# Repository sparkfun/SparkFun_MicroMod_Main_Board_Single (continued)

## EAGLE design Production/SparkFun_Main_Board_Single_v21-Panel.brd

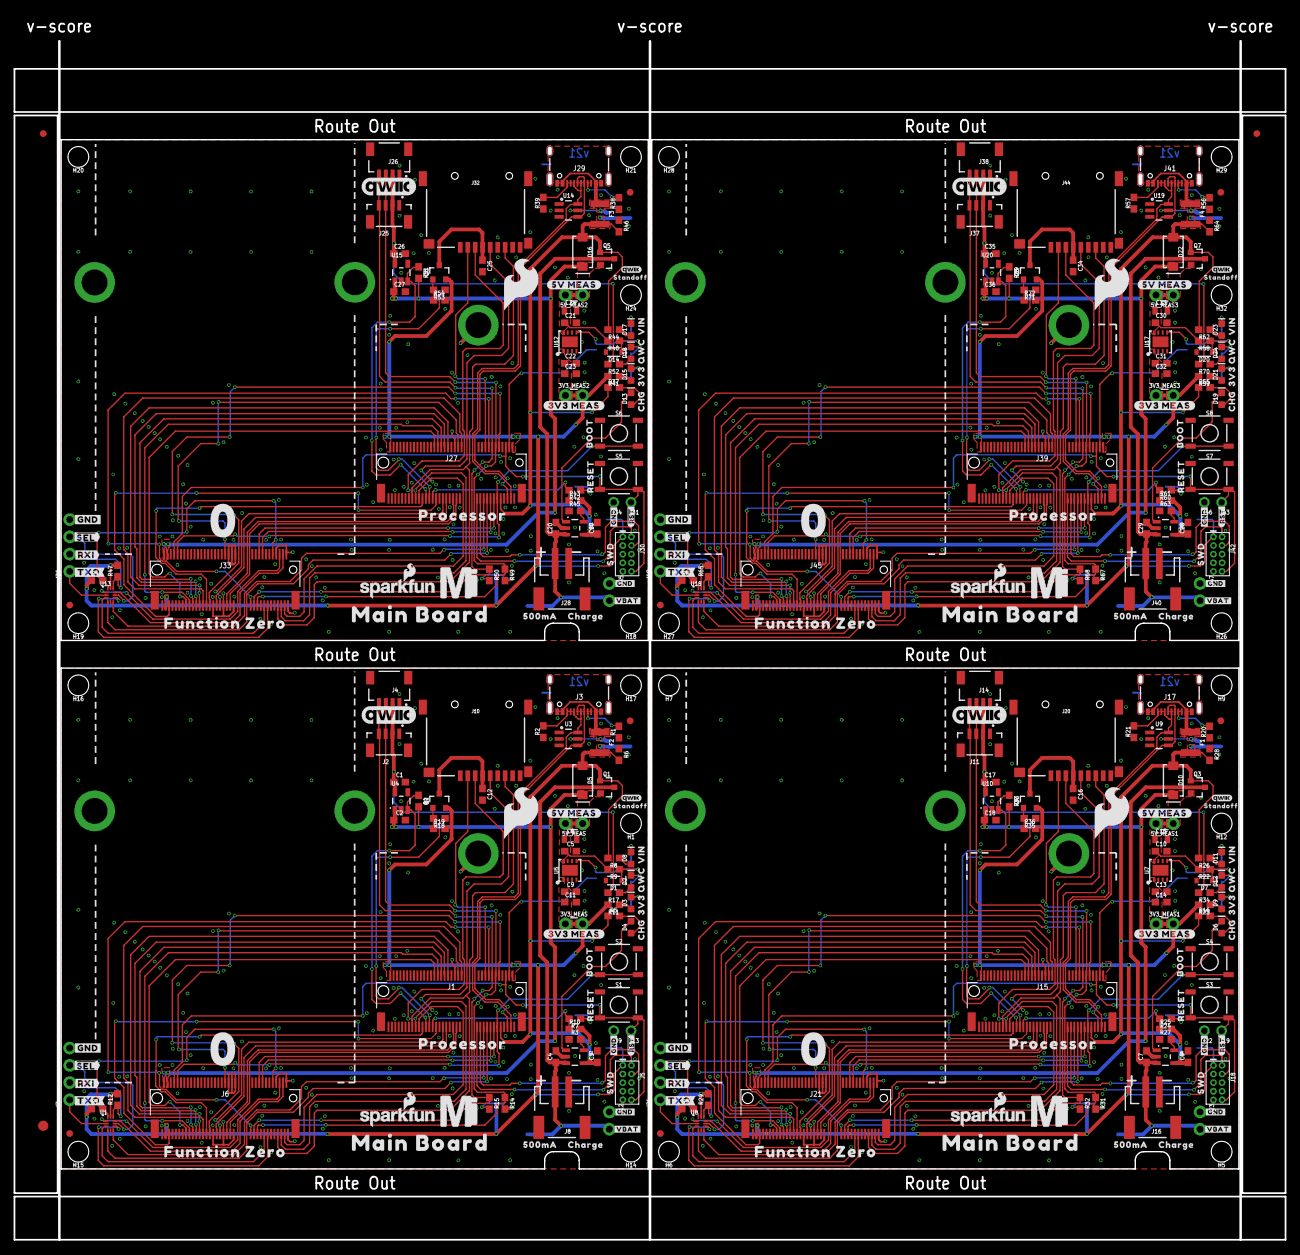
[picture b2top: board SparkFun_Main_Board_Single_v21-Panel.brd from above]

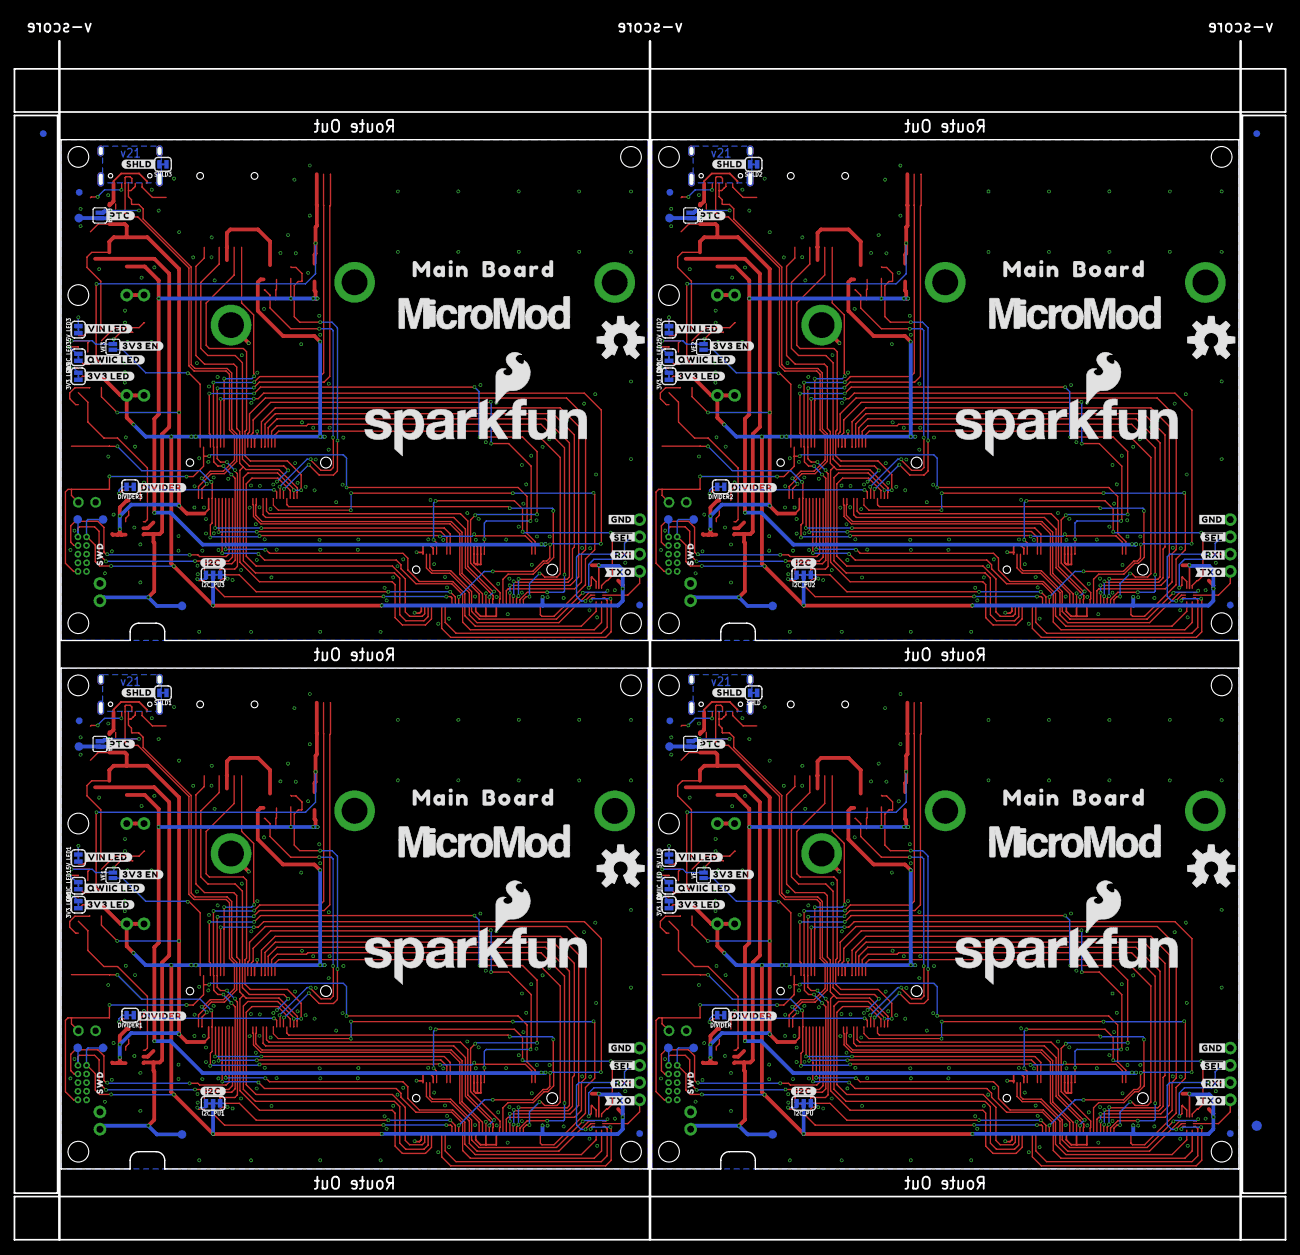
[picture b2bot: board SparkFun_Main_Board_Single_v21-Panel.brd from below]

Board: 2 copper layers, 186.9 x 176.3 mm, 518 parts (131 on the bottom side), 280 nets.

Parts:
3V3_LED, 3V3_LED1, 3V3_LED2, 3V3_LED3, 5V_LED, 5V_LED1, 5V_LED2, 5V_LED3: JUMPER-SMT_2_NC_TRACE_SILK; SMT-JUMPER_2_NC_TRACE_SILK
3V3_MEAS, 3V3_MEAS1, 3V3_MEAS2, 3V3_MEAS3, 5V_MEAS, 5V_MEAS1, 5V_MEAS2, 5V_MEAS3: JUMPER-COMBO_2_NC_TRACE; COMBO-JUMPER_2_NC_TRACE
BYP, BYP1, BYP2, BYP3: JUMPER-SMT_2_NO_SILK; SMT-JUMPER_2_NO_SILK
C1, C2, C17, C18, C26, C27, C35, C36: 1.0uF; 0603
C3, C4, C6, C7, C11, C14, C19, C20, C23, C28, C29, C32: 4.7uF; 0603
C5, C10, C21, C30: 0.1uF; 0603
C8, C15, C24, C33: 10uF; 0805
C9, C12, C13, C16, C22, C25, C31, C34: 10uF; 0603
D1, D7, D14, D20: 3.3V; SOD-323
D2, D3, D8, D9, D11, D12, D15, D17, D18, D21, D23, D24: RED; LED-0603
D4, D6, D13, D19: Yellow; LED-0603
D5, D10, D16, D22: 3A/40V/500mV; SMA-DIODE
DIVIDER, DIVIDER1, DIVIDER2, DIVIDER3: JUMPER-SMT_2_NC_TRACE_SILK; SMT-JUMPER_2_NC_TRACE_SILK
E$1, E$2, E$3, E$4: FIDUCIAL-1X2
E$5, E$6: FIDUCIAL-1.5X3
F1, F2, F3, F4: 6V/2A; 1210
FD1, FD2, FD3, FD4, FD5, FD6, FD7, FD8, FD9, FD10, FD11, FD12, FD13, FD14, FD15, FD16: FIDUCIAL1X2; FIDUCIAL-1X2
H1, H5, H6, H7, H9, H12, H14, H15, H16, H17, H18, H19, H20, H21, H24, H26, H27, H28, H29, H32: STAND-OFFTIGHT; STAND-OFF-TIGHT
H2, H3, H4, H8, H10, H11, H13, H22, H23, H25, H30, H31: STAND-OFF-REFLOW-M2.5_2.5MM_TALL; STAND-OFF-REFLOW-M2.5
I2C_PU, I2C_PU1, I2C_PU2, I2C_PU3: JUMPER-SMT_3_2-NC_TRACE_SILK; SMT-JUMPER_3_2-NC_TRACE_SILK
J1, J15, J27, J39: MICROMOD-2222-C; M.2-CONNECTOR-E
J2, J11, J25, J37: Vertical Qwiic Connector; JST04_1MM_VERT
J3, J17, J29, J41: USB-C-16P-2LAYER-PADS
J4, J14, J26, J38: QWIIC_RIGHT_ANGLE; JST04_1MM_RA
J5, J18, J30, J42: CORTEX_JTAG_DEBUG_MINIMUM_PTH; 2X5-PTH-1.27MM
J6, J21, J33, J45: MICROMOD_FUNCTION_MAIN; M.2-CONNECTOR-E-FUNCTION-STANDARD
J7, J24, J36, J48: 1X04_NO_SILK
J8, J16, J28, J40: JST-2-SMD
J9, J13, J19, J22, J31, J34, J43, J46: 1X01_NO_SILK
J10, J20, J32, J44: MICRO-SD-PUSH-PUSH-EXT-PIN; MICROSD-EXTERNALPIN
J12, J23, J35, J47: 1X02_NO_SILK
LOGO1, LOGO4, LOGO7, LOGO10: QWIIC_LOGO_8MM; QWIIC_8MM
LOGO2, LOGO5, LOGO8, LOGO11: SFE_LOGO_NAME_FLAME.3_INCH; SFE_LOGO_NAME_FLAME_.3
LOGO3, LOGO6, LOGO9, LOGO12: OSHW-LOGOL; OSHW-LOGO-L
Q1, Q3, Q5, Q7: 3.1A/30V/105mΩ; SOT23-3
Q2, Q4, Q6, Q8: 20V/4.2A/52mΩ/1.4W; SOT23-3
QWIIC_LED, QWIIC_LED1, QWIIC_LED2, QWIIC_LED3: JUMPER-SMT_2_NC_TRACE_SILK; SMT-JUMPER_2_NC_TRACE_SILK
R1, R2, R20, R21, R38, R39, R56, R57: 5.1k; 0603
R3, R27, R45, R63: 2.0k; 0603
R4, R9, R12, R13, R19, R22, R29, R30, R33, R36, R40, R47, R48, R51, R54, R58, R65, R66, R69, R72: 100k; 0603
R5, R16, R37, R55: 4.7k; 0603
R6, R7, R24, R28, R42, R46, R60, R64: 10k; 0603
R8, R14, R15, R26, R31, R32, R44, R49, R50, R62, R67, R68: 2.2k; 0603
R10, R25, R43, R61: 20k; 0603
R11, R17, R23, R34, R41, R52, R59, R70: 1k; 0603
R18, R35, R53, R71: 100; 0603
S1, S3, S5, S7: Reset; TACTILE_SWITCH_SMD_5.2MM
S2, S4, S6, S8: BOOT; TACTILE_SWITCH_SMD_5.2MM
SHLD, SHLD1, SHLD2, SHLD3: JUMPER-SMT_2_NC_TRACE_SILK; SMT-JUMPER_2_NC_TRACE_SILK
TP1, TP2, TP3, TP4, TP5, TP6, TP7, TP8, TP9, TP10, TP11, TP12, TP13, TP14, TP15, TP16: TEST-POINT3X5; PAD.03X.05
U1, U8, U13, U18: STG3856QTR; STG3856
U2, U6, U11, U16: MCP73831; SOT23-5
U3, U9, U14, U19: ESD Diode; SOT-23-6
U4, U10, U15, U20: AP7347DQ-33W5-7K-3.3V; SOT25
U5, U7, U12, U17: AP7361C-33; UDFN-8
U$1, U$78, U$122, U$166: #TXO#7
U$2, U$79, U$123, U$167: #RXI#6
U$3, U$84, U$128, U$172: #PTC#15
U$4, U$40, U$89, U$133: 3V332533
U$5, U$41, U$90, U$134: VIN32532
U$6, U$42, U$91, U$135: CHG32531
U$7, U$62, U$106, U$150: #SHLD#501
U$8, U$43, U$92, U$136: BOOT32541
U$9, U$44, U$93, U$137: RESET32540
U$10, U$45, U$94, U$138: PROCESSOR525
U$11, U$46, U$95, U$139: FUNCTION_ZERO520
U$12, U$80, U$124, U$168: ##SEL##5
U$13, U$54, U$98, U$142: MAIN523
U$14, U$47, U$96, U$140: MICROMOD_MI_LOGO_1
U$15, U$48, U$97, U$141: 0523
U$16, U$29, U$73, U$74, U$117, U$118, U$161, U$162: #GND#3
U$17, U$57, U$101, U$145: MICROMOD_LOGO_1
U$18, U$55, U$99, U$143: BOARD524
U$19, U$81, U$125, U$169: ##SEL##3
U$20, U$82, U$126, U$170: #RXI#4
U$21, U$56, U$100, U$144: MAIN_BOARD5523
U$22, U$58, U$102, U$146: QWIIC_3MM
U$23, U$59, U$103, U$147: STANDOFF501
U$24, U$60, U$104, U$148: SFE_LOGO_FLAME_.3
U$25, U$32, U$66, U$75, U$110, U$119, U$154, U$163: SWD6522
U$26, U$63, U$107, U$151: #3V3_MEAS#6522
U$27, U$61, U$105, U$149: CHARGE501
U$28, U$83, U$127, U$171: #TXO#5
U$30, U$72, U$116, U$160: #I2C#501
U$31, U$64, U$108, U$152: #5V_MEAS#6522
U$33, U$65, U$109, U$153: 500MA6520
U$34, U$76, U$120, U$164: SFE_LOGO_NAME_FLAME_.1
U$35, U$77, U$121, U$165: QWC4
U$36, U$37, U$85, U$86, U$129, U$130, U$173, U$174: #GND#10
U$38, U$87, U$131, U$175: ##RST##8
U$39, U$88, U$132, U$176: #VBAT#9
U$49, U$67, U$111, U$155: #3V3_EN#23
U$50, U$68, U$112, U$156: #3V3_LED#22
U$51, U$69, U$113, U$157: #QWIIC_LED#22
U$52, U$70, U$114, U$158: #DIVIDER#23
U$53, U$71, U$115, U$159: #VIN_LED#24
VE, VE1, VE2, VE3: JUMPER-SMT_2_NO_SILK; SMT-JUMPER_2_NO_SILK

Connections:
3.3V: 3V3_MEAS.2, 3V3_MEAS.4, I2C_PU.2, J1.2, J1.74, J5.1, J6.73, Q2.2, R11.2, R12.2, R13.1, TP2.1, U1.P11
3.3V1: 3V3_MEAS1.2, 3V3_MEAS1.4, I2C_PU1.2, J15.2, J15.74, J18.1, J21.73, Q4.2, R23.2, R29.2, R30.1, TP5.1, U8.P11
3.3V2: 3V3_MEAS2.2, 3V3_MEAS2.4, I2C_PU2.2, J27.2, J27.74, J30.1, J33.73, Q6.2, R41.2, R47.2, R48.1, TP9.1, U13.P11
3.3V3: 3V3_MEAS3.2, 3V3_MEAS3.4, I2C_PU3.2, J39.2, J39.74, J42.1, J45.73, Q8.2, R59.2, R65.2, R66.1, TP13.1, U18.P11
3.3V_EN: J1.4, VE.1
3.3V_EN1: J15.4, VE1.1
3.3V_EN2: J27.4, VE2.1
3.3V_EN3: J39.4, VE3.1
3.3V_EN_VE: D1.C, R9.1, U5.5, VE.2
3.3V_EN_VE1: D7.C, R22.1, U7.5, VE1.2
3.3V_EN_VE2: D14.C, R40.1, U12.5, VE2.2
3.3V_EN_VE3: D20.C, R58.1, U17.5, VE3.2
3.3V_QWIIC: C1.1, J2.2, J4.2, R17.2, U4.5
3.3V_QWIIC1: C17.1, J11.2, J14.2, R34.2, U10.5
3.3V_QWIIC2: C26.1, J25.2, J26.2, R52.2, U15.5
3.3V_QWIIC3: C35.1, J37.2, J38.2, R70.2, U20.5
3V3_MEAS: 3V3_MEAS.1, 3V3_MEAS.3, C9.1, C11.1, U5.1
3V3_MEAS1: 3V3_MEAS1.1, 3V3_MEAS1.3, C13.1, C14.1, U7.1
3V3_MEAS2: 3V3_MEAS2.1, 3V3_MEAS2.3, C22.1, C23.1, U12.1
3V3_MEAS3: 3V3_MEAS3.1, 3V3_MEAS3.3, C31.1, C32.1, U17.1
!BOOT!: J1.11, J6.66, S2.3, S2.4
!BOOT!1: J15.11, J21.66, S4.3, S4.4
!BOOT!2: J27.11, J33.66, S6.3, S6.4
!BOOT!3: J39.11, J45.66, S8.3, S8.4
!CS0!-PROCESSOR: J1.55, J6.49
!CS0!-PROCESSOR1: J15.55, J21.49
!CS0!-PROCESSOR2: J27.55, J33.49
!CS0!-PROCESSOR3: J39.55, J45.49
!DFU-FC0!: J6.10, R13.2, U1.P12
!DFU-FC0!1: J21.10, R30.2, U8.P12
!DFU-FC0!2: J33.10, R48.2, U13.P12
!DFU-FC0!3: J45.10, R66.2, U18.P12
!RESET!: J1.6, J5.10, J6.68, J13.1, S1.3, S1.4
!RESET!1: J15.6, J18.10, J19.1, J21.68, S3.3, S3.4
!RESET!2: J27.6, J30.10, J31.1, J33.68, S5.3, S5.4
!RESET!3: J39.6, J42.10, J43.1, J45.68, S7.3, S7.4
!SEL!/2IN: J7.3, R12.1, U1.P10
!SEL!/2IN1: J24.3, R29.1, U8.P10
!SEL!/2IN2: J36.3, R47.1, U13.P10
!SEL!/2IN3: J48.3, R65.1, U18.P10
A0-PROCESSOR: J1.34, J6.38
A0-PROCESSOR1: J15.34, J21.38
A0-PROCESSOR2: J27.34, J33.38
A0-PROCESSOR3: J39.34, J45.38
CTS1-PROCESSOR: J1.15, J6.16
CTS1-PROCESSOR1: J15.15, J21.16
CTS1-PROCESSOR2: J27.15, J33.16
CTS1-PROCESSOR3: J39.15, J45.16
D0-PROCESSOR: J1.10, J6.47
D0-PROCESSOR1: J15.10, J21.47
D0-PROCESSOR2: J27.10, J33.47
D0-PROCESSOR3: J39.10, J45.47
D1-PROCESSOR/SD_CARD_!CS!: J1.18, J10.2
D1-PROCESSOR/SD_CARD_!CS!1: J15.18, J20.2
D1-PROCESSOR/SD_CARD_!CS!2: J27.18, J32.2
D1-PROCESSOR/SD_CARD_!CS!3: J39.18, J44.2
D+: J1.3, J3.A6, J3.B6, U3.6
D+1: J15.3, J17.A6, J17.B6, U9.6
D+2: J27.3, J29.A6, J29.B6, U14.6
D+3: J39.3, J41.A6, J41.B6, U19.6
D-: J1.5, J3.A7, J3.B7, U3.4
D-1: J15.5, J17.A7, J17.B7, U9.4
D-2: J27.5, J29.A7, J29.B7, U14.4
D-3: J39.5, J41.A7, J41.B7, U19.4
G0-PROCESSOR: J1.40, J6.53
G0-PROCESSOR1: J15.40, J21.53
G0-PROCESSOR2: J27.40, J33.53
G0-PROCESSOR3: J39.40, J45.53
G1-PROCESSOR: J1.42, J6.55
G1-PROCESSOR1: J15.42, J21.55
G1-PROCESSOR2: J27.42, J33.55
G1-PROCESSOR3: J39.42, J45.55
G2-PROCESSOR: J1.44, J6.57
G2-PROCESSOR1: J15.44, J21.57
G2-PROCESSOR2: J27.44, J33.57
G2-PROCESSOR3: J39.44, J45.57
G3-PROCESSOR: J1.46, J6.59
G3-PROCESSOR1: J15.46, J21.59
G3-PROCESSOR2: J27.46, J33.59
G3-PROCESSOR3: J39.46, J45.59
G4-PROCESSOR: J1.48, J6.61
G4-PROCESSOR1: J15.48, J21.61
G4-PROCESSOR2: J27.48, J33.61
G4-PROCESSOR3: J39.48, J45.61
GND: 3V3_LED.1, 5V_LED.1, C1.2, C2.2, C3.2, C4.2, C5.2, C8.2, C9.2, C11.2, C12.2, D1.A, DIVIDER.1, H2.1, H4.1, H8.1, J1.1, J1.7, J1.33, J1.36, J1.39, J1.45, J1.75, J2.1, J3.GND, J3.GND2, J4.1, J5.3, J5.5, J5.9, J6.1, J6.2, J6.8, J6.32, J6.33, J6.34, J6.36, J6.39, J6.45, J6.75, J7.4, J8.1, J9.1, J10.6, J10.10, J10.11, J10.12, J10.13, J12.1, QWIIC_LED.1, R1.1, R2.1, R3.1, R6.1, R19.2, S1.1, S1.2, S2.1, S2.2, SHLD.1, U1.P5, U2.2, U3.2, U4.2, U5.4, U5.EP
GND1: 3V3_LED1.1, 5V_LED1.1, C6.2, C7.2, C10.2, C13.2, C14.2, C15.2, C16.2, C17.2, C18.2, D7.A, DIVIDER1.1, H3.1, H10.1, H11.1, J11.1, J14.1, J15.1, J15.7, J15.33, J15.36, J15.39, J15.45, J15.75, J16.1, J17.GND, J17.GND2, J18.3, J18.5, J18.9, J20.6, J20.10, J20.11, J20.12, J20.13, J21.1, J21.2, J21.8, J21.32, J21.33, J21.34, J21.36, J21.39, J21.45, J21.75, J22.1, J23.1, J24.4, QWIIC_LED1.1, R20.1, R21.1, R27.1, R28.1, R36.2, S3.1, S3.2, S4.1, S4.2, SHLD1.1, U6.2, U7.4, U7.EP, U8.P5, U9.2, U10.2
GND2: 3V3_LED2.1, 5V_LED2.1, C19.2, C20.2, C21.2, C22.2, C23.2, C24.2, C25.2, C26.2, C27.2, D14.A, DIVIDER2.1, H13.1, H22.1, H23.1, J25.1, J26.1, J27.1, J27.7, J27.33, J27.36, J27.39, J27.45, J27.75, J28.1, J29.GND, J29.GND2, J30.3, J30.5, J30.9, J32.6, J32.10, J32.11, J32.12, J32.13, J33.1, J33.2, J33.8, J33.32, J33.33, J33.34, J33.36, J33.39, J33.45, J33.75, J34.1, J35.1, J36.4, QWIIC_LED2.1, R38.1, R39.1, R45.1, R46.1, R54.2, S5.1, S5.2, S6.1, S6.2, SHLD2.1, U11.2, U12.4, U12.EP, U13.P5, U14.2, U15.2
GND3: 3V3_LED3.1, 5V_LED3.1, C28.2, C29.2, C30.2, C31.2, C32.2, C33.2, C34.2, C35.2, C36.2, D20.A, DIVIDER3.1, H25.1, H30.1, H31.1, J37.1, J38.1, J39.1, J39.7, J39.33, J39.36, J39.39, J39.45, J39.75, J40.1, J41.GND, J41.GND2, J42.3, J42.5, J42.9, J44.6, J44.10, J44.11, J44.12, J44.13, J45.1, J45.2, J45.8, J45.32, J45.33, J45.34, J45.36, J45.39, J45.45, J45.75, J46.1, J47.1, J48.4, QWIIC_LED3.1, R56.1, R57.1, R63.1, R64.1, R72.2, S7.1, S7.2, S8.1, S8.2, SHLD3.1, U16.2, U17.4, U17.EP, U18.P5, U19.2, U20.2
HOST_D+: J1.35, J6.35
HOST_D+1: J15.35, J21.35
HOST_D+2: J27.35, J33.35
HOST_D+3: J39.35, J45.35
HOST_D-: J1.37, J6.37
HOST_D-1: J15.37, J21.37
HOST_D-2: J27.37, J33.37
HOST_D-3: J39.37, J45.37
I2C_!INT!: J1.16, J6.23
I2C_!INT!1: J15.16, J21.23
I2C_!INT!2: J27.16, J33.23
I2C_!INT!3: J39.16, J45.23
I2C_SCL: J1.14, J2.4, J4.4, J6.21, R15.1
I2C_SCL1: J11.4, J14.4, J15.14, J21.21, R32.1
I2C_SCL1-PROCESSOR/QWIIC_EN: J1.53, R4.1, U4.3
I2C_SCL1-PROCESSOR/QWIIC_EN1: J15.53, R33.1, U10.3
I2C_SCL1-PROCESSOR/QWIIC_EN2: J27.53, R51.1, U15.3
I2C_SCL1-PROCESSOR/QWIIC_EN3: J39.53, R69.1, U20.3
I2C_SCL2: J25.4, J26.4, J27.14, J33.21, R50.1
I2C_SCL3: J37.4, J38.4, J39.14, J45.21, R68.1
I2C_SDA: J1.12, J2.3, J4.3, J6.19, R14.1
I2C_SDA1: J11.3, J14.3, J15.12, J21.19, R31.1
I2C_SDA1-PROCESSOR/!SD_ENABLE!: J1.51, R18.1
I2C_SDA1-PROCESSOR/!SD_ENABLE!1: J15.51, R35.1
I2C_SDA1-PROCESSOR/!SD_ENABLE!2: J27.51, R53.1
I2C_SDA1-PROCESSOR/!SD_ENABLE!3: J39.51, R71.1
I2C_SDA2: J25.3, J26.3, J27.12, J33.19, R49.1
I2C_SDA3: J37.3, J38.3, J39.12, J45.19, R67.1
unnamed: J17.B5, R21.2
unnamed: 5V_LED.2, D8.C
unnamed: D3.A, R11.1
unnamed: J3.B5, R2.2
unnamed: J3.A5, R1.2
unnamed: R3.2, U2.5
unnamed: DIVIDER.2, R7.1
unnamed: D4.C, U2.1
unnamed: D4.A, R5.2
unnamed: 3V3_LED.2, D3.C
unnamed: I2C_PU.3, R14.2
unnamed: D8.A, R8.1
unnamed: I2C_PU.1, R15.2
unnamed: D2.A, R17.1
unnamed: D2.C, QWIIC_LED.2
unnamed: C12.1, J10.4, Q2.3
unnamed: J17.A5, R20.2
unnamed: Q2.1, R18.2, R19.1
unnamed: D9.A, R23.1
unnamed: D11.A, R26.1
unnamed: 5V_LED1.2, D11.C
unnamed: 3V3_LED1.2, D9.C
unnamed: I2C_PU1.3, R31.2
unnamed: I2C_PU1.1, R32.2
unnamed: R27.2, U6.5
unnamed: DIVIDER1.2, R24.1
unnamed: D6.C, U6.1
unnamed: D6.A, R16.2
unnamed: D12.A, R34.1
unnamed: D12.C, QWIIC_LED1.2
unnamed: Q4.1, R35.2, R36.1
unnamed: C16.1, J20.4, Q4.3
unnamed: J29.B5, R39.2
unnamed: J29.A5, R38.2
unnamed: D15.A, R41.1
unnamed: D17.A, R44.1
unnamed: 5V_LED2.2, D17.C
unnamed: 3V3_LED2.2, D15.C
unnamed: I2C_PU2.3, R49.2
unnamed: I2C_PU2.1, R50.2
unnamed: R45.2, U11.5
unnamed: DIVIDER2.2, R42.1
unnamed: D13.C, U11.1
unnamed: D13.A, R37.2
unnamed: D18.A, R52.1
unnamed: D18.C, QWIIC_LED2.2
unnamed: Q6.1, R53.2, R54.1
unnamed: C25.1, J32.4, Q6.3
unnamed: J41.B5, R57.2
unnamed: J41.A5, R56.2
unnamed: D21.A, R59.1
unnamed: D23.A, R62.1
unnamed: 5V_LED3.2, D23.C
unnamed: 3V3_LED3.2, D21.C
unnamed: I2C_PU3.3, R67.2
unnamed: I2C_PU3.1, R68.2
unnamed: R63.2, U16.5
unnamed: DIVIDER3.2, R60.1
unnamed: D19.C, U16.1
unnamed: D19.A, R55.2
unnamed: D24.A, R70.1
unnamed: D24.C, QWIIC_LED3.2
unnamed: Q8.1, R71.2, R72.1
unnamed: C34.1, J44.4, Q8.3
PROCESSOR_CAN-RX: J1.41, J6.43
PROCESSOR_CAN-RX1: J15.41, J21.43
PROCESSOR_CAN-RX2: J27.41, J33.43
PROCESSOR_CAN-RX3: J39.41, J45.43
PROCESSOR_CAN-TX: J1.43, J6.41
PROCESSOR_CAN-TX1: J15.43, J21.41
PROCESSOR_CAN-TX2: J27.43, J33.41
PROCESSOR_CAN-TX3: J39.43, J45.41
PWM0-PROCESSOR: J1.32, J6.51
PWM0-PROCESSOR1: J15.32, J21.51
PWM0-PROCESSOR2: J27.32, J33.51
PWM0-PROCESSOR3: J39.32, J45.51
PWR_EN0: J1.47, J6.71
PWR_EN1: J15.47, J21.71
PWR_EN2: J27.47, J33.71
PWR_EN3: J39.47, J45.71
RTS1-PROCESSOR: J1.13, J6.18
RTS1-PROCESSOR1: J15.13, J21.18
RTS1-PROCESSOR2: J27.13, J33.18
RTS1-PROCESSOR3: J39.13, J45.18
RX1-DFU_TX-FC0-PLEX: J6.4, U1.P9
RX1-DFU_TX-FC0-PLEX1: J21.4, U8.P9
RX1-DFU_TX-FC0-PLEX2: J33.4, U13.P9
RX1-DFU_TX-FC0-PLEX3: J45.4, U18.P9
RX1-PROCESSOR: J1.19, U1.P6
RX1-PROCESSOR1: J15.19, U8.P6
RX1-PROCESSOR2: J27.19, U13.P6
RX1-PROCESSOR3: J39.19, U18.P6
RX1-PROCESSOR-PLEX: J6.13, U1.P7
RX1-PROCESSOR-PLEX1: J21.13, U8.P7
RX1-PROCESSOR-PLEX2: J33.13, U13.P7
RX1-PROCESSOR-PLEX3: J45.13, U18.P7
RX1/2S1: J24.2, U8.P8
RX1/2S2: J7.2, U1.P8
RX1/2S3: J36.2, U13.P8
RX1/2S4: J48.2, U18.P8
SHLD: J3.SHLD1, J3.SHLD2, J3.SHLD3, J3.SHLD4, SHLD.2
SHLD1: J17.SHLD1, J17.SHLD2, J17.SHLD3, J17.SHLD4, SHLD1.2
SHLD2: J29.SHLD1, J29.SHLD2, J29.SHLD3, J29.SHLD4, SHLD2.2
SHLD3: J41.SHLD1, J41.SHLD2, J41.SHLD3, J41.SHLD4, SHLD3.2
SPI_PROCESSOR_SCK: J1.57, J6.3, J10.5
SPI_PROCESSOR_SCK1: J15.57, J20.5, J21.3
SPI_PROCESSOR_SCK2: J27.57, J32.5, J33.3
SPI_PROCESSOR_SCK3: J39.57, J44.5, J45.3
SPI_PROCESSOR_SDI: J1.61, J6.7, J10.7
SPI_PROCESSOR_SDI1: J15.61, J20.7, J21.7
SPI_PROCESSOR_SDI2: J27.61, J32.7, J33.7
SPI_PROCESSOR_SDI3: J39.61, J44.7, J45.7
SPI_PROCESSOR_SDO: J1.59, J6.5, J10.3
SPI_PROCESSOR_SDO1: J15.59, J20.3, J21.5
SPI_PROCESSOR_SDO2: J27.59, J32.3, J33.5
SPI_PROCESSOR_SDO3: J39.59, J44.3, J45.5
SWDCK: J1.21, J5.4
SWDCK1: J15.21, J18.4
SWDCK2: J27.21, J30.4
SWDCK3: J39.21, J42.4
SWDIO: J1.23, J5.2, TP1.1
SWDIO1: J15.23, J18.2, TP8.1
SWDIO2: J27.23, J30.2, TP12.1
SWDIO3: J39.23, J42.2, TP16.1
TX1-DFU_RX-FC0-PLEX: J6.6, U1.P1
TX1-DFU_RX-FC0-PLEX1: J21.6, U8.P1
TX1-DFU_RX-FC0-PLEX2: J33.6, U13.P1
TX1-DFU_RX-FC0-PLEX3: J45.6, U18.P1
TX1-PROCESSOR: J1.17, U1.P4
TX1-PROCESSOR1: J15.17, U8.P4
TX1-PROCESSOR2: J27.17, U13.P4
TX1-PROCESSOR3: J39.17, U18.P4
TX1-PROCESSOR-PLEX: J6.15, U1.P3
TX1-PROCESSOR-PLEX1: J21.15, U8.P3
TX1-PROCESSOR-PLEX2: J33.15, U13.P3
TX1-PROCESSOR-PLEX3: J45.15, U18.P3
TX1/1S1: J24.1, U8.P2
TX1/1S2: J7.1, U1.P2
TX1/1S3: J36.1, U13.P2
TX1/1S4: J48.1, U18.P2
VCC: 5V_MEAS.1, 5V_MEAS.3, C2.1, D5.C, J6.72, J6.74, Q1.2, R4.2, U4.1
VCC1: 5V_MEAS1.1, 5V_MEAS1.3, C18.1, D10.C, J21.72, J21.74, Q3.2, R33.2, U10.1
VCC2: 5V_MEAS2.1, 5V_MEAS2.3, C27.1, D16.C, J33.72, J33.74, Q5.2, R51.2, U15.1
VCC3: 5V_MEAS3.1, 5V_MEAS3.3, C36.1, D22.C, J45.72, J45.74, Q7.2, R69.2, U20.1
VCC_MEAS: 5V_MEAS.2, 5V_MEAS.4, C5.1, C8.1, R9.2, U5.8
VCC_MEAS1: 5V_MEAS1.2, 5V_MEAS1.4, C10.1, C15.1, R22.2, U7.8
VCC_MEAS2: 5V_MEAS2.2, 5V_MEAS2.4, C21.1, C24.1, R40.2, U12.8
VCC_MEAS3: 5V_MEAS3.2, 5V_MEAS3.4, C30.1, C33.1, R58.2, U17.8
VIN: BYP.2, C3.1, D5.A, F2.2, J1.9, Q1.1, R5.1, R6.2, R8.2, R10.2, TP4.1, U2.4
VIN1: BYP1.2, C6.1, D10.A, F1.2, J15.9, Q3.1, R16.1, R25.2, R26.2, R28.2, TP7.1, U6.4
VIN2: BYP2.2, C19.1, D16.A, F3.2, J27.9, Q5.1, R37.1, R43.2, R44.2, R46.2, TP11.1, U11.4
VIN3: BYP3.2, C28.1, D22.A, F4.2, J39.9, Q7.1, R55.1, R61.2, R62.2, R64.2, TP15.1, U16.4
VIN/1: J15.49, R24.2, R25.1
VIN/2: J27.49, R42.2, R43.1
VIN/3: J1.49, R7.2, R10.1
VIN/4: J39.49, R60.2, R61.1
V_BATT: C4.1, J8.2, J12.2, Q1.3, TP3.1, U2.3
V_BATT1: C7.1, J16.2, J23.2, Q3.3, TP6.1, U6.3
V_BATT2: C20.1, J28.2, J35.2, Q5.3, TP10.1, U11.3
V_BATT3: C29.1, J40.2, J47.2, Q7.3, TP14.1, U16.3
V_USB: BYP.1, F2.1, J3.VBUS1, J3.VBUS2, U3.5
V_USB1: BYP1.1, F1.1, J17.VBUS1, J17.VBUS2, U9.5
V_USB2: BYP2.1, F3.1, J29.VBUS1, J29.VBUS2, U14.5
V_USB3: BYP3.1, F4.1, J41.VBUS1, J41.VBUS2, U19.5
